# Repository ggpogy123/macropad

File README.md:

# Custom Macropad
A custom-designed macropad board using Raspberry Pi Pico 2, dual rotary encoders, three switches and a dedicated 1.8 inch SPI display.

## Visuals

## Hardware Specifications
* **Microcontroller:** Raspberry Pi Pico 2
* **Display:** 1.8-inch TFT LCD Module (SPI Interface)
* **Inputs:** 3x Buildcon Blue Mechanical Keyswitches & 2x Flyrobo EC11 15mm Rotary Encoders
* **Knobs & Keycaps:** 2x Black Aluminum Alloy 19x19mm Screw-Type Knobs & Trendivibe PBT MA Profile Ball Shape Keycaps
* **PCB Specs:** 2-layer FR4, 124.0 x 104.0 mm, 1.6mm thickness

## Key Design Features
* **Using Berg strip:** Things are fully socketed using Berg strips, allowing for easy swapping, testing and safety during soldering.
* **Ground Plane:** A dedicated copper pour layer has been used across the layout to connect all GND points.

## Pin layout

### Display (J1)

| Pin Name | Connection Type | Pico pin | Working |
| :--- | :--- | :--- | :--- |
| 3V3 | Power | 3V3 | Power |
| GND | Ground | GND | Ground |
| DISP_CS | SPI Chip Select | GPIO 9 | Chip Select |
| DISP_RESET | Shared Reset | GPIO 13 | Hardware Reset |
| DISP_DC | Digital Output | GPIO 12 | Data/Command |
| SPI_MOSI | SPI Data | GPIO 15 | Master Out Slave In |
| SPI_SCK | SPI Clock | GPIO 14 | Serial Clock |
| 3V3 | Power | 3V3 | Backlight |

### Switches

| Pin Name | Connection Type | Pico pin | Working |
| :--- | :--- | :--- | :--- |
| KEY_BACK | Digital Input | GPIO 0 | SW1  |
| KEY_PAUSE | Digital Input | GPIO 1 | SW2  |
| KEY_NEXT | Digital Input | GPIO 2 | SW3  |

### Encoders

| Pin Name | Connection Type | Pico pin | Working |
| :--- | :--- | :--- | :--- |
| ENC1_A | Digital Input | GPIO 3 | Rotary 1 Phase A |
| ENC1_B | Digital Input | GPIO 4 | Rotary 1 Phase B |
| ENC1_SW | Digital Input | GPIO 5 | Rotary 1 Click |
| ENC2_A | Digital Input | GPIO 6 | Rotary 2 Phase A |
| ENC2_B | Digital Input | GPIO 7 | Rotary 2 Phase B |
| ENC2_SW | Digital Input | GPIO 8 | Rotary 2 Click |

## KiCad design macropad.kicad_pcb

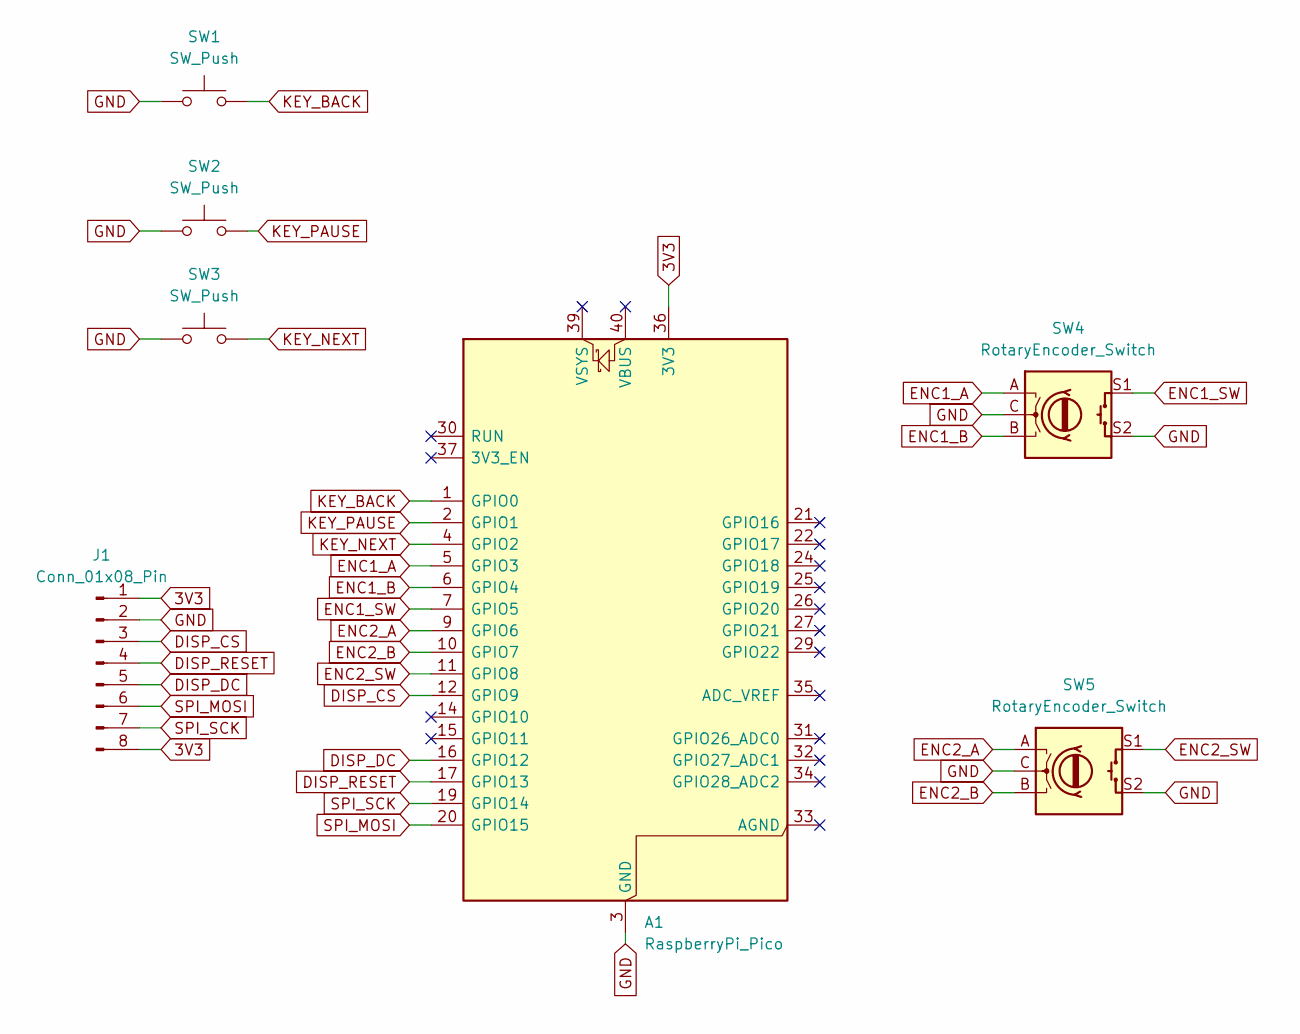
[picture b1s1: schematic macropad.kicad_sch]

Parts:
A1: RaspberryPi_Pico; RaspberryPi_Pico_Common_THT
J1: Conn_01x08_Pin; PinSocket_1x08_P2.54mm_Vertical
SW1, SW2, SW3: SW_Push; SW_Cherry_MX_1.00u_Plate
SW4, SW5: RotaryEncoder_Switch; RotaryEncoder_Alps_EC11E-Switch_Vertical_H20mm

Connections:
3V3: A1.36 (3V3), J1.1, J1.8
DISP_CS: A1.12 (GPIO9), J1.3
DISP_DC: A1.16 (GPIO12), J1.5
DISP_RESET: A1.17 (GPIO13), J1.4
ENC1_A: A1.5 (GPIO3), SW4.A
ENC1_B: A1.6 (GPIO4), SW4.B
ENC1_SW: A1.7 (GPIO5), SW4.S1
ENC2_A: A1.9 (GPIO6), SW5.A
ENC2_B: A1.10 (GPIO7), SW5.B
ENC2_SW: A1.11 (GPIO8), SW5.S1
GND: A1.3 (GND), A1.8 (GND), A1.13 (GND), A1.18 (GND), A1.23 (GND), A1.28 (GND), A1.38 (GND), J1.2, SW1.1, SW2.1, SW3.1, SW4.C, SW4.S2, SW5.C, SW5.S2
KEY_BACK: A1.1 (GPIO0), SW1.2
KEY_NEXT: A1.4 (GPIO2), SW3.2
KEY_PAUSE: A1.2 (GPIO1), SW2.2
SPI_MOSI: A1.20 (GPIO15), J1.6
SPI_SCK: A1.19 (GPIO14), J1.7

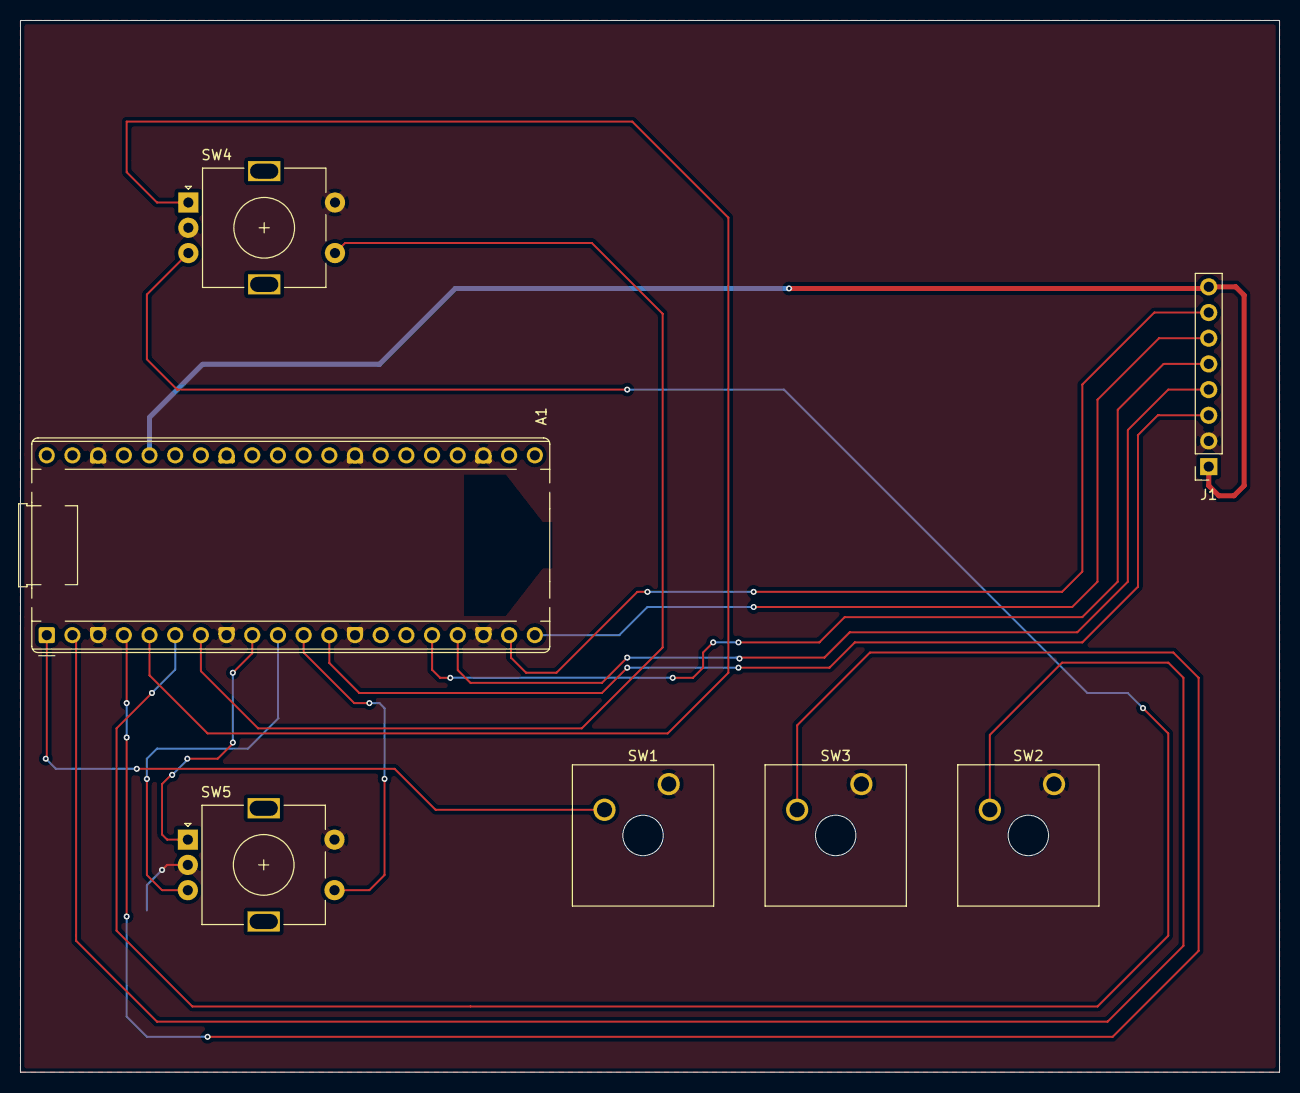
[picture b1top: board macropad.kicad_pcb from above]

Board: 2 copper layers, 124.5 x 104.0 mm, 7 parts (0 on the bottom side), 16 nets.
